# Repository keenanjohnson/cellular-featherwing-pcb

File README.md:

# cellular-featherwing-pcb
The PCB Design for a Cellular Adafruit Featherwing based on the Quectel BG96 LTE Cat M1 &amp; Cat NB1.

Based on the excellent [qTop Adafruit Feather design](https://www.iot-bots.com/collections/qtop-cellular/products/qtop-adafruit-feather-compatible-lte-cat-m1-nb-iot-gnss-shield) by [IOT-BOTS](https://www.iot-bots.com/)

# Current Status
This PCB is currently being produced by [JLPCB](https://jlcpcb.com/). The design has NOT been verified as functional yet until first production samples are tested.

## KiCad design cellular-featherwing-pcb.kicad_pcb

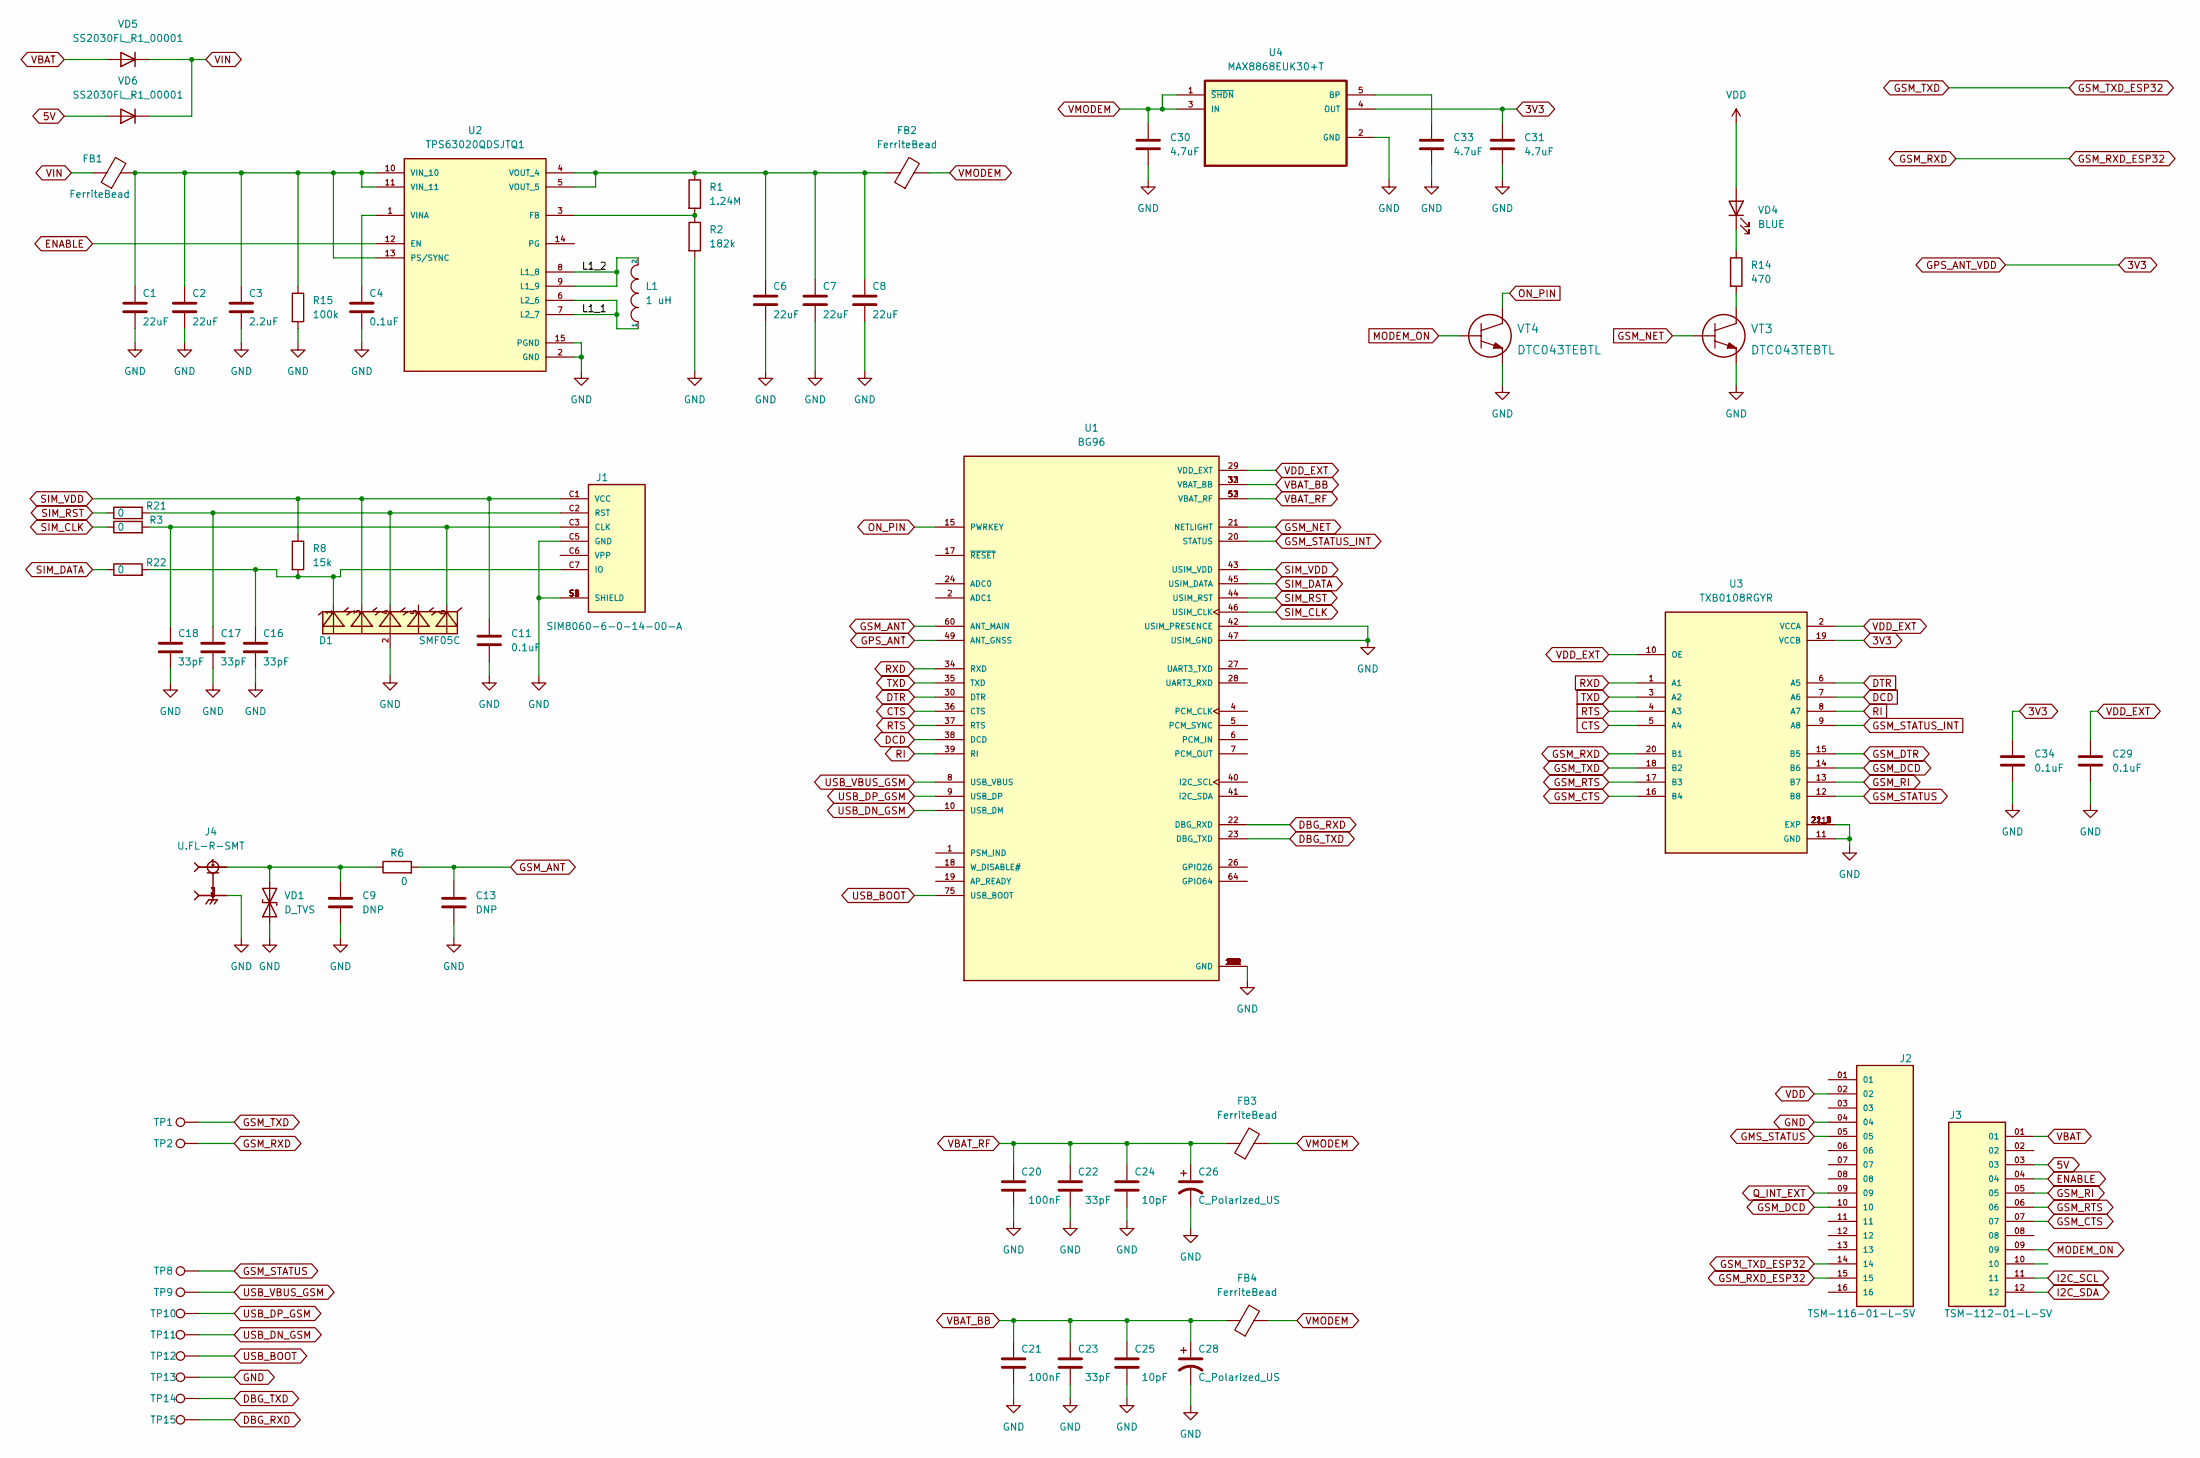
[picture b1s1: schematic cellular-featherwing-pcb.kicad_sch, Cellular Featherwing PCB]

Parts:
C1, C2, C6, C7, C8: 22uF; C_0603_1608Metric; MPN GCM1885C2A220JA16D; LCSC C415703
C3: 2.2uF; C_0402_1005Metric; MPN CL05A225MQ5NSNC; LCSC C12530
C4, C11, C29, C34: 0.1uF; C_0402_1005Metric; MPN CL05B104KO5NNNC; LCSC C1525
C9, C13: DNP; C_0402_1005Metric; MPN DNP; LCSC DNP
C16, C17, C18, C22, C23: 33pF; C_0402_1005Metric; MPN 0402CG330J500NT; LCSC C1562
C20, C21: 100nF; C_0402_1005Metric; MPN CL05B104KO5NNNC; LCSC C1525
C24, C25: 10pF; C_0402_1005Metric; MPN CL05C100JB5NNNC; LCSC C32949
C26, C28: C_Polarized_US; CP_EIA-3528-12_Kemet-T; MPN T490B337M006ATE800; LCSC C347529
C30, C31, C33: 4.7uF; C_0402_1005Metric; MPN CL05A475MP5NRNC; LCSC C23733
D1: SMF05C; SC70-6; MPN SMF05C.TCT; LCSC C85191
FB1, FB2, FB3, FB4: FerriteBead; R_0805_2012Metric; MPN 742792030; LCSC C15957
J1: SIM8060-6-0-14-00-A; GCT_SIM8060-6-0-14-00-A; MPN SIM8060-6-0-14-00-A; LCSC C111371
J2: TSM-116-01-L-SV; SAMTEC_TSM-116-01-L-SV; MPN TSM-116-01-L-SV
J3: TSM-112-01-L-SV; SAMTEC_TSM-112-01-L-SV; MPN TSM-112-01-L-SV
J4: U.FL-R-SMT; HRS_U.FL-R-SMT(10); MPN U.FL-R-SMT(10); LCSC C434808
L1: 1 uH; L_Coilcraft_XxL4020; MPN XGL4020-102MEC
R1: 1.24M; R_0402_1005Metric; MPN RC0402FR-071M24L; LCSC C166533
R2: 182k; R_0402_1005Metric; MPN AC0402FR-07182KL; LCSC C226822
R3, R6, R21, R22: 0; R_0402_1005Metric; MPN 0402WGF0000TCE; LCSC C17168
R8: 15k; R_0402_1005Metric; MPN 0402WGF1502TCE; JLCPCB 0402WGF1502TCE
R14: 470; C_0402_1005Metric; MPN 0402WGF4700TCE; JLCPCB 0402WGF4700TCE
R15: 100k; R_0402_1005Metric; MPN 0402WGF1003TCE; JLCPCB 0402WGF1003TCE
TP1, TP2, TP8, TP9, TP10, TP11, TP12, TP13, TP14, TP15: TestPoint; TestPoint_Pad_D1.0mm; MPN DNP; LCSC DNP
U1: BG96; Quectel_BG96; PARTREV 1.4; LCSC C3010493
U2: TPS63020QDSJTQ1; IC_TPS63020DSJR; MPN TPS63020QDSJTQ1; LCSC C202140
U3: TXB0108RGYR; IC_TXB0108RGYR; PARTREV H; JLCPCB Part #（optional ) C194701
U4: MAX8868EUK30+T; SOT95P280X145-5N; MPN MAX8868EUK30+T; LCSC C37970
VD1: D_TVS; D_0402_1005Metric; MPN EZA-EG2A50AX; LCSC C316053
VD4: BLUE; LED_0603_1608Metric; MPN 150060BS75000; LCSC C72041
VD5, VD6: SS2030FL_R1_00001; D_SOD-123F; MPN SS2030FL_R1_00001; LCSC C167645
VT3, VT4: DTC043TEBTL; SOT-23; MPN DTC043TEBTL; LCSC C2971747

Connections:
3V3: C31.1, C34.1, U3.19 (VCCB), U4.4 (OUT)
5V: J3.03, VD6.2 (A)
/L1_1: L1.1, U2.6 (L2_6), U2.7 (L2_7)
/L1_2: L1.2, U2.8 (L1_8), U2.9 (L1_9)
CTS: U1.36 (CTS), U3.5 (A4)
DBG_RXD: TP15.1, U1.22 (DBG_RXD)
DBG_TXD: TP14.1, U1.23 (DBG_TXD)
DCD: U1.38 (DCD), U3.7 (A6)
DTR: U1.30 (DTR), U3.6 (A5)
ENABLE: J3.04, U2.12 (EN)
GMS_STATUS: J2.05
GND: C1.2, C2.2, C3.2, C4.2, C6.2, C7.2, C8.2, C9.2, C11.2, C13.2, C16.2, C17.2, C18.2, C20.2, C21.2, C22.2, C23.2, C24.2, C25.2, C26.2, C28.2, C29.2, C30.2, C31.2, C33.2, C34.2, D1.2, J1.C5 (GND), J1.S1 (SHIELD), J1.S2 (SHIELD), J1.S3 (SHIELD), J1.S4 (SHIELD), J2.04, J4.2, J4.3, R2.2, R15.2, TP13.1, U1.3 (GND), U1.31 (GND), U1.42 (USIM_PRESENCE), U1.47 (USIM_GND), U1.48 (GND), U1.50 (GND), U1.54 (GND), U1.55 (GND), U1.58 (GND), U1.59 (GND), U1.61 (GND), U1.62 (GND), U1.67 (GND), U1.68 (GND), U1.69 (GND), U1.70 (GND), U1.71 (GND), U1.72 (GND), U1.73 (GND), U1.74 (GND), U1.79 (GND), U1.80 (GND), U1.81 (GND), U1.82 (GND), U1.89 (GND), U1.90 (GND), U1.91 (GND), U1.100 (GND), U1.101 (GND), U1.102 (GND), U2.2 (GND), U2.15 (PGND), U3.11 (GND), U3.21 (EXP), U3.21_1 (EXP), U3.21_2 (EXP), U3.21_3 (EXP), U3.21_4 (EXP), U4.2 (GND), VD1.1 (A1), VT3.2, VT4.2
GPS_ANT: U1.49 (ANT_GNSS)
GSM_ANT: C13.1, R6.2, U1.60 (ANT_MAIN)
GSM_CTS: J3.07, U3.16 (B4)
GSM_DCD: J2.10, U3.14 (B6)
GSM_DTR: U3.15 (B5)
GSM_NET: U1.21 (NETLIGHT), VT3.1
GSM_RI: J3.05, U3.13 (B7)
GSM_RTS: J3.06, U3.17 (B3)
GSM_RXD: J2.15, TP2.1, U3.20 (B1)
GSM_STATUS: TP8.1, U3.12 (B8)
GSM_STATUS_INT: U1.20 (STATUS), U3.9 (A8)
GSM_TXD: J2.14, TP1.1, U3.18 (B2)
I2C_SCL: J3.11
I2C_SDA: J3.12
MODEM_ON: J3.09, VT4.1
unnamed: C1.1, C2.1, C3.1, FB1.2, R15.1, U2.10 (VIN_10), U2.11 (VIN_11), U2.13 (PS/SYNC)
unnamed: C4.1, U2.1 (VINA)
unnamed: C6.1, C7.1, C8.1, FB2.1, R1.1, U2.4 (VOUT_4), U2.5 (VOUT_5)
unnamed: C9.1, J4.1, R6.1, VD1.2 (A2)
unnamed: C16.1, D1.1, J1.C7 (IO), R8.2, R22.2
unnamed: C17.1, D1.4, J1.C2 (RST), R21.2
unnamed: C18.1, D1.6, J1.C3 (CLK), R3.2
unnamed: C33.1, U4.5 (BP)
unnamed: R1.2, R2.1, U2.3 (FB)
unnamed: R14.1, VD4.1 (K)
unnamed: R14.2, VT3.3
ON_PIN: U1.15 (PWRKEY), VT4.3
Q_INT_EXT: J2.09
RI: U1.39 (RI), U3.8 (A7)
RTS: U1.37 (RTS), U3.4 (A3)
RXD: U1.34 (RXD), U3.1 (A1)
SIM_CLK: R3.1, U1.46 (USIM_CLK)
SIM_DATA: R22.1, U1.45 (USIM_DATA)
SIM_RST: R21.1, U1.44 (USIM_RST)
SIM_VDD: C11.1, D1.3, J1.C1 (VCC), R8.1, U1.43 (USIM_VDD)
TXD: U1.35 (TXD), U3.3 (A2)
USB_BOOT: TP12.1, U1.75 (USB_BOOT)
USB_DN_GSM: TP11.1, U1.10 (USB_DM)
USB_DP_GSM: TP10.1, U1.9 (USB_DP)
USB_VBUS_GSM: TP9.1, U1.8 (USB_VBUS)
VBAT: J3.01, VD5.2 (A)
VBAT_BB: C21.1, C23.1, C25.1, C28.1, FB4.1, U1.32 (VBAT_BB), U1.33 (VBAT_BB)
VBAT_RF: C20.1, C22.1, C24.1, C26.1, FB3.1, U1.52 (VBAT_RF), U1.53 (VBAT_RF)
VDD: J2.02, VD4.2 (A)
VDD_EXT: C29.1, U1.29 (VDD_EXT), U3.2 (VCCA), U3.10 (OE)
VIN: FB1.1, VD5.1 (K), VD6.1 (K)
VMODEM: C30.1, FB2.2, FB3.2, FB4.2, U4.1 (~SHDN), U4.3 (IN)

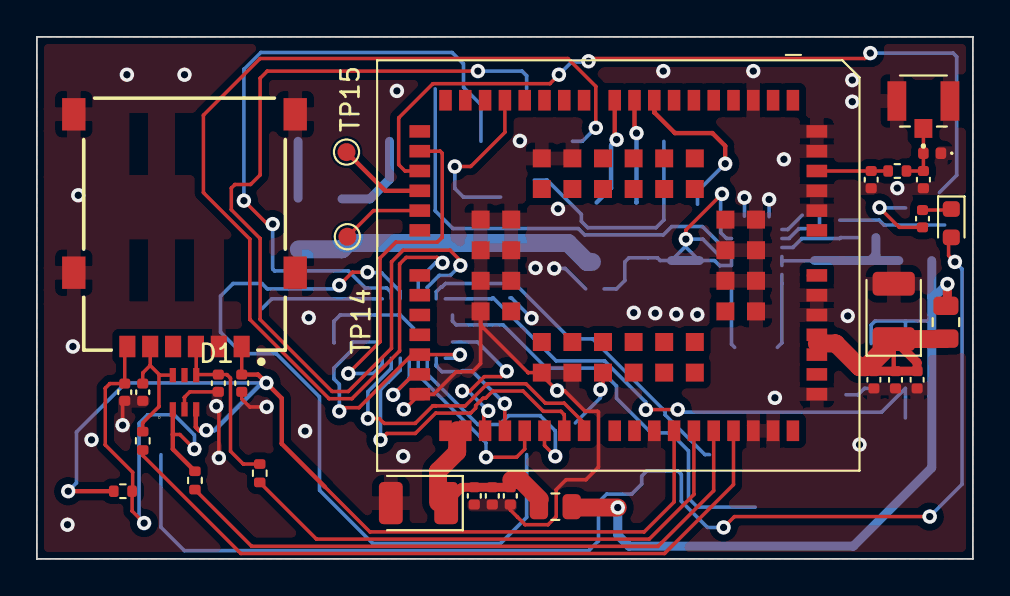
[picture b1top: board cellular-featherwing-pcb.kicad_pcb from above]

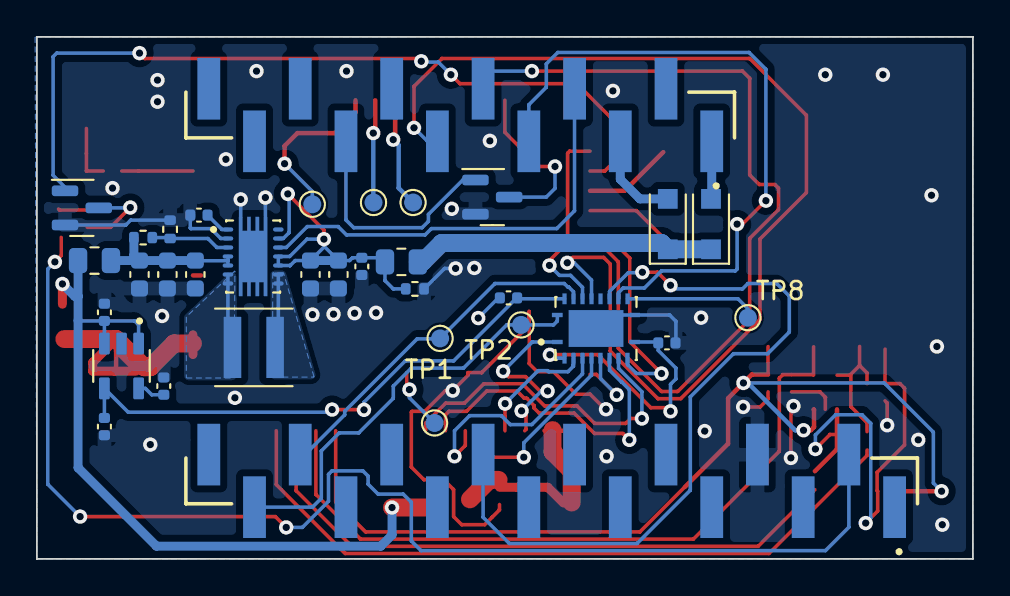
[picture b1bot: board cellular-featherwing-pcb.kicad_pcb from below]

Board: 2 copper layers, 52.0 x 29.0 mm, 64 parts (34 on the bottom side), 53 nets.

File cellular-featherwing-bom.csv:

Comment,Designator,Footprint,JLCPCB Part #（optional）,
22uF,"C1,C2,C6,C7,C8",22 uF 0603 Capacitor,C59461,
2.2uF,C3,2.2 uF 0402 Capacitor,C12530,
0.1uF,"C4,C11,C29,C34",0.1 uF 0402 Capacitor,C1525,
33pF,"C16,C17,C18,C22,C23",33 pF 0402 Capacitor,C1562,
100nF,"C20,C21",100 nF 0402 Capacitor,C1525,
10pF,"C24,C25",10 pF 0402 Capacitor,C32949,
C_Polarized_US,"C26,C28",330 碌F Molded Tantalum Capacitors 6 V 1411 (3528 Metric) 800mOhm,C347529,
4.7uF,"C30,C31,C33",4.7 碌F 卤20% 10V Ceramic Capacitor X5R 0402 (1005 Metric),C23733,
SMF05C,D1,12.5V Clamp 8A (8/20碌s) Ipp Tvs Diode Surface Mount SC-70-6,C85191,
0 Ohm Resistor,"FB1,FB2,FB3,FB4",0805 (2012 Metric) 0 Ohm Resistor,C269721,
SIM8060-6-0-14-00-A,J1,"SIM NANO HINGED, 6P, 1.40MM PROF",C111371,
TSM-116-01-L-SV,J2,"Connector Header Surface Mount 16 position 0.100"" (2.54mm)",,
TSM-112-01-L-SV,J3,"Connector Header Surface Mount 12 position 0.100"" (2.54mm)",,
U.FL-R-SMT,J4,"U.FL (UMCC) Connector Receptacle, Male Pin 50Ohm Surface Mount Solder",C88373,
1 uH,L1,1 碌H Shielded Molded Inductor 12 A 9mOhm Max 1616 (4040 Metric),,
1.24M,R1,1.24M Ohm 0402 Resistor,C166533,
182k,R2,182k Ohm 0402 Resistor,C226822,
0,"R3,R6,R21,R22",0 Ohm 0402 Resistor,C17168,
15k,R8,15k Ohm 0402 Resistor,C25756,
470,R14,470 Ohm 0402 Resistor,C25117,
100k,R15,100k Ohm 0402 Resistor,C25741,
BG96,U1,Quectel BG96 Cellular Module,C3010493,
TPS63020DSJR,U2,High Efficiency Single Inductor Buck-Boost Converter with 4A Switch 14-VSON -40 to 85,C15483,
TXB0108RGYR,U3,TXB0108 8-Bit Bidirectional Voltage-Level Translator,C194701,
MAX8868EUK30+T,U4,Linear Voltage Regulator IC Positive Fixed 1 Output 150mA SOT-23-5,"C37970
",
D_TVS,VD1,"Varistor 1 Circuit Surface Mount, MLCV 0402 (1005 Metric)",C316053,
BLUE,VD4,Blue 470nm LED Indication - Discrete 3.2V 0603 (1608 Metric),C72041,
SS2030FL_R1_00001,"VD5,VD6",Diode 30 V 2A Surface Mount SOD-123FL,C167645,
DDTD123YC-7-F,"VT3,VT4",NPN PRE-BIASED 500mA SURFACE MOUNT TRANSISTOR,C280842,

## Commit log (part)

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2023-01-14 Project start: Blank files
2023-01-14 .gitignore: Remove .DS_Store files
2023-01-14 snapeda: Adding bg96
2023-01-14 Add Bg96 to schematic
2023-01-14 Add CI Kibot Stuff
2023-01-14 CI: Disable BOM
2023-01-14 .gitignore: Ignore kicad backups
2023-01-15 Footprints for all major components
2023-01-15 Fix CI Run
2023-01-15 Add board outline
2023-01-15 Fix 3D model for bg96
2023-01-15 Add pn for gate
2023-01-15 Routing progress
2023-01-15 Add ufl connector
2023-01-15 Wired up bg96 in schematic
2023-01-15 schematic updates
2023-01-15 More progress
2023-01-15 Schematic updates for sim card
2023-01-15 Added attribution and removed license
2023-01-15 finished schematic for sim card
2023-01-15 Wired network LED in schematic
2023-01-15 Wired all the jumpers
2023-01-15 Work on jumpers
2023-01-16 schematic complete
2023-01-16 All footprints assigned
2023-01-16 Fixed drc and imported to pcb
2023-01-17 starting component layout
2023-01-17 Placement work
2023-01-17 Finished board outline and feather placements
2023-01-17 Placed quectel
2023-01-18 Parts placement
2023-01-18 Placed all components
2023-01-25 All components placed
2023-01-25 permanently linked 3d model
2023-01-25 Small updates
2023-01-25 Add auto save files to gitignore
2023-02-02 Updates from Javier
2023-02-02 Updated board from javier
2023-02-03 All items routed
2023-02-03 Clean DRC
2023-02-03 Routing complete
2023-02-03 DRC and 3D Model Adjustments
2023-02-03 Add part numbers and BOM
2023-02-03 add bom
2023-02-03 Update BOM
2023-02-03 POS Files
2023-02-03 Adding lcsc part numbers for jlpcb
2023-02-03 Files sent to jlpcb
2023-02-04 Update u.fl lcsc part number
2023-02-04 Updates for jlpcb
2023-02-04 Adding gerbers
2023-02-05 Updated small footprint for pcb production
2023-02-05 Added image
2023-02-14 #1 Connected LED
2023-02-14 New fab files
2023-02-14 Update npn transitor
2023-02-14 Updated gerbers
2023-02-14 Updated bom back to tps63020dsjr and 3.8 volts
2023-02-15 Fixed duplicate r1 in BOM
